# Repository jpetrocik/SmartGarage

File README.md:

# SmartGarage

SmartGarage is a WIFI enabled device that works with most garage door openers. Along with opening and closing the garage door, it provides the current status of the door, whether its open or closed.  The stock firmware provides both a HTTP Restful api and MQTT based interface. No 3rd party servers are required for SmartGarage to work, you can directly operate it via a HTTP RestAPI or MQTT.  It easly intergrates with HomeAssistant, https://www.home-assistant.io/ and other home automation software.

## Controlling The Garage Door ##

RESTful Api

```
GET  http://garage.local/
Returns the current status of the door, e.g. open or closed

GET  http://garage.local/door
Operates the door, either closing it or opening it depending on what the current status is.

GET http://garage.local/config
Returns the current configuration

PUT http://garage.local/config?poperty_name=property_value
Sets the configuration property to the provided value

GET http://garage.local/restart
Reboot the device

POST http://garage.local/factoryreset
Resets the device to factory settings
```

MQTT

MQTT is a common messaging protocol used for IoT devices.  Most home automation systems like OpenHab and home-assistant.io  support mqtt messaging. If you are unfamiliar with MQTT, check out https://mosquitto.org/ to learn more.

The device listens on the command topic and publishes the status of the door on the status topic.  The command topic is used to send commands to the device to operate the garage door. The default hostname for the device is __garage__, below replace [hostname] with the hostname of the device.  If you have not changed it, it will be __garage__. 

```
garage/[hostname]/command
```

The messages published to the command topic are very simple,  just numeric numbers.  You can request the door to close, open, or toggle depending on its current state.
```
0 Close the door 
1 Open the door 
2 Toggle the door, open or close depending on current state
3 Request current status
```

If you are using mosquito the command line to open the garage door would look like this:

```
mosquito_pub -t garage/garage/command -m 1
```

When the door opens or closes, the status is published on the status topic.  The message is a json message indicating the current status.  Again, if using mosquito the command line to listen for the status change would be

```
mosquito_sub -t garage/garage/status 
```

Here is an example of the message published with the door is closed.

```
{
  "status": "CLOSED"
}
```

## Installation Guide ##

https://docs.google.com/document/d/12LUHNYjrVlYSZdDVwD1QsqcnY-EzrYETPhFzhXXMPhE/edit?usp=sharing

## Device ##

The physical PCB is about 20mm x 40mm and is powered by a mini usb cable.  Installation is straight forward and does not interfere the current operation of the garage door, all remotes and openers still work.

There are a couple options to get your hands on your own board.  You can order it directly from me on ebay.com with the latest firmware already flashed and ready to install, or you can download the Eagle files from https://github.com/jpetrocik/SmartGarage and build your own.

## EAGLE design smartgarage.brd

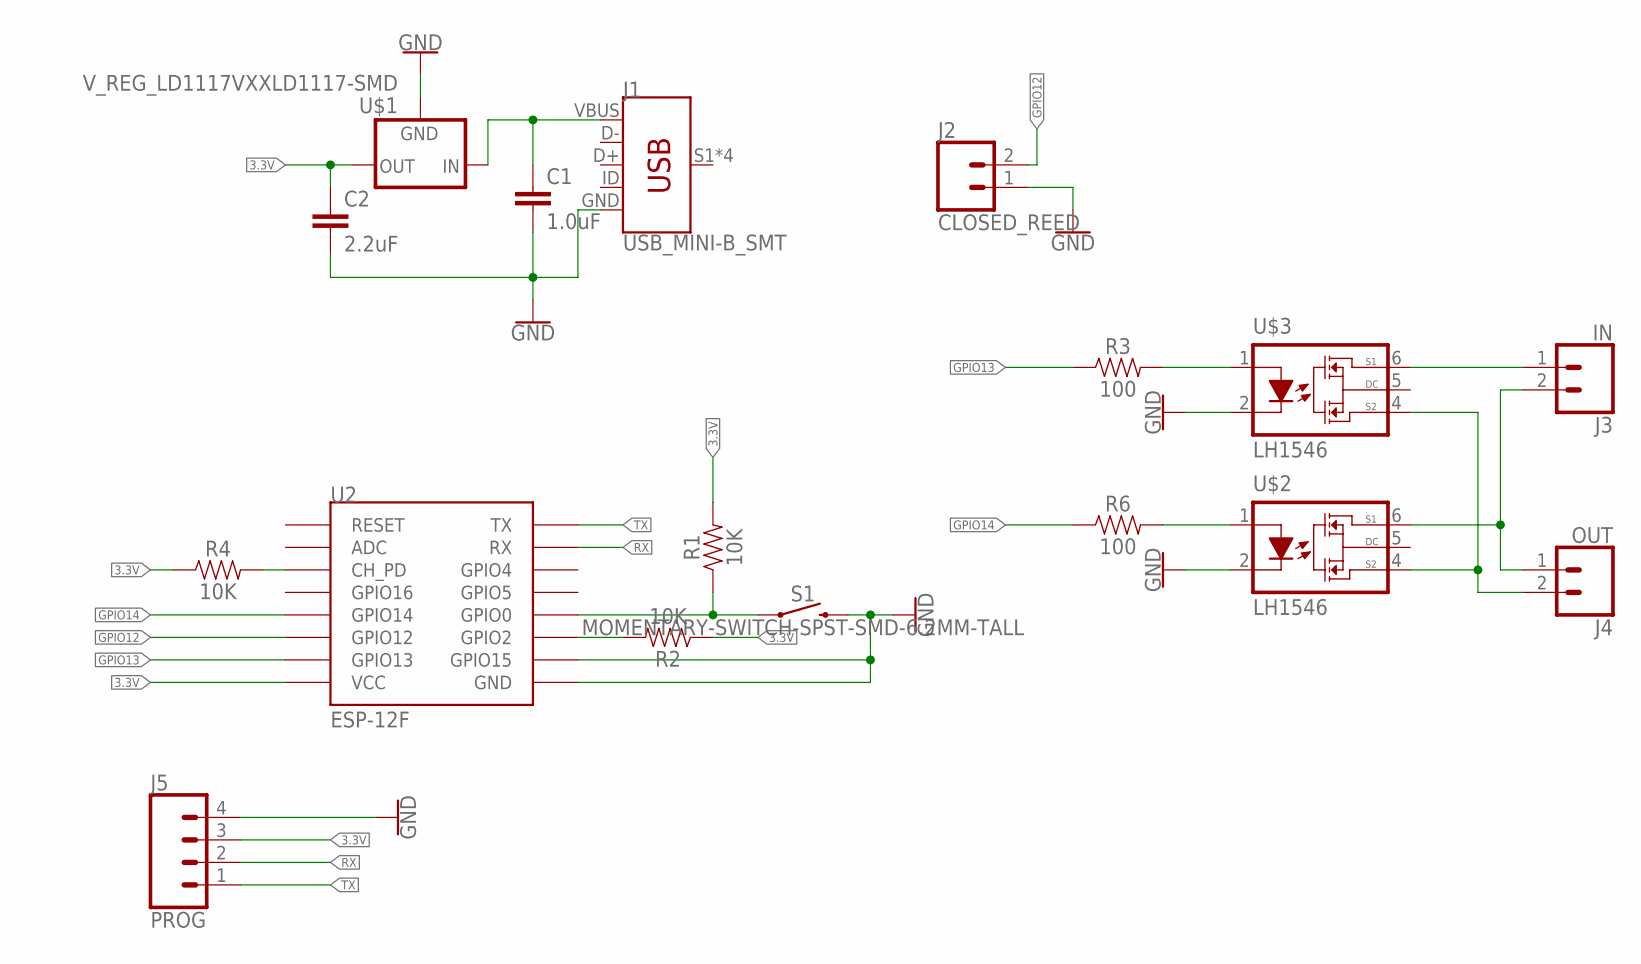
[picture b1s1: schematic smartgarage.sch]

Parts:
C1: 1.0uF; 0805
C2: 2.2uF; 0805
J1: USB_MINI-B_SMT; USB-MINIB
J2: CLOSED_REED; SCREWTERMINAL-3.5MM-2-NS
J3: IN; SCREWTERMINAL-3.5MM-2-NS
J4: OUT; SCREWTERMINAL-3.5MM-2-NS
J5: PROG; 1X04
R1, R2, R4: 10K; 0805
R3, R6: 100; 0805
S1: MOMENTARY-SWITCH-SPST-SMD-6.2MM-TALL; TACTILE_SWITCH_SMD_6.2MM_TALL
U2: ESP-12F; ESP12-SMD
U$1: V_REG_LD1117VXXLD1117-SMD; SOT223
U$2, U$3: LH1546; DIL6-SMD

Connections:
3.3V: C2.1, J5.3, R1.2, R2.1, R4.1, U2.VCC, U$1.2 (OUT)
GND: C1.2, C2.2, J1.GND, J2.1, J5.4, S1.B2 (2), U2.GND, U2.GPIO15, U$1.1 (GND), U$2.2 (C), U$3.2 (C)
GPIO12: J2.2, U2.GPIO12
GPIO13: R3.1, U2.GPIO13
GPIO14: R6.1, U2.GPIO14
unnamed: R1.1, S1.A2 (1), U2.GPIO0
unnamed: R6.2, U$2.1 (A)
unnamed: R4.2, U2.CH_PD
unnamed: R2.2, U2.GPIO2
unnamed: J3.2, J4.1, U$2.6 (S1)
unnamed: R3.2, U$3.1 (A)
unnamed: J3.1, U$3.6 (S1)
unnamed: J4.2, U$2.4 (S2), U$3.4 (S2)
RX: J5.2, U2.RXD0 (RX)
TX: J5.1, U2.TXD0 (TX)
VBUS: C1.1, J1.VBUS, U$1.3 (IN)

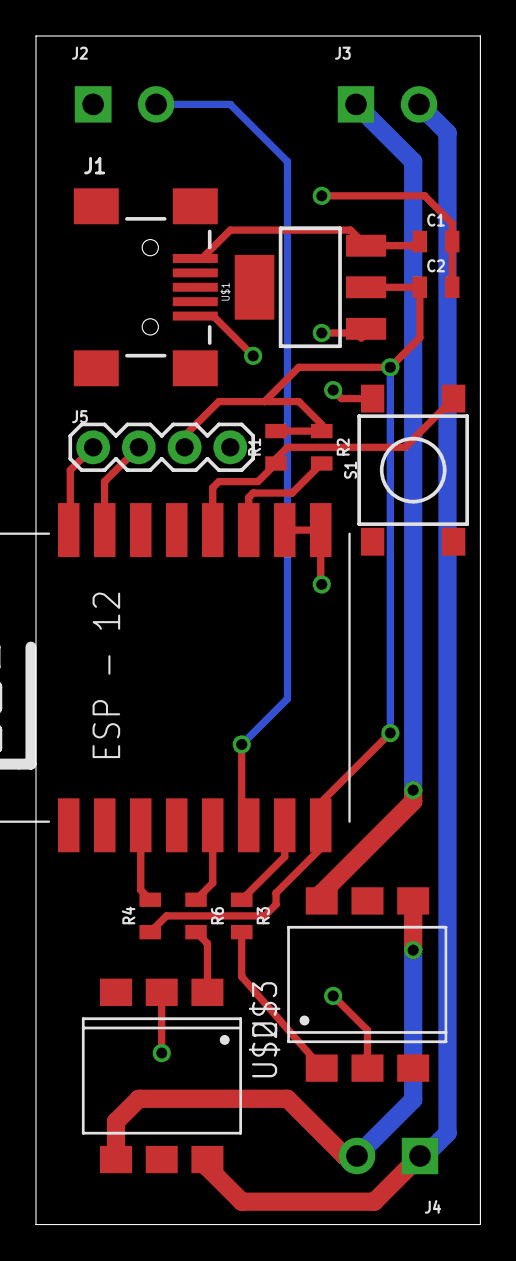
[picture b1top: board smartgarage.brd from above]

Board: 2 copper layers, 24.7 x 66.0 mm, 17 parts (0 on the bottom side), 16 nets.

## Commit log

2019-03-12 V1.2 - Rotated ESP, add lock
2019-03-14 Adding firmward to project
2019-03-14 First draft of read.MD
2019-03-15 Cleaned up device description
2019-03-15 Add support for both secure and unsecure mqtt
2019-03-15 Added image of device
2019-08-10 Updated for v1.2
2019-08-25 Hardware 1.2.1, moved screw terminal

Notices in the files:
parts and their libraries:
SparkFun-Capacitors: Licensing: Creative Commons ShareAlike 4.0 International - https://creativecommons.org/licenses/by-sa/4.0
